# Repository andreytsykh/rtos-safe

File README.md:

# RTOS Safe

> Модель електронного сейфу на ESP32-S3 і FreeRTOS, у якому перезавантаження
> контролера не скидає лічильник невдалих PIN-спроб та активне alarm
> блокування.

## Можливості

- FSM: `LOCKED → ENTERING_CODE → OPEN / ALARM → LOCKED`.
- Введення PIN енкодером із кнопкою та інтерфейс на OLED.
- Три LED, пасивний бузер, реле й SG90 для фізичної індикації та замка.
- Тригодинний `ALARM` після трьох неправильних PIN-кодів.
- Відновлення PIN, лічильника спроб і deadline `ALARM` із FRAM та RTC.
- Миттєве авторизоване скидання `ALARM` NFC-карткою.
- Журнал спроб доступу в окремому розділі flash.
- Структуровані експериментальні Serial-логи з тегом `SAFE_TEST`.

## Апаратна платформа

| Компонент | Призначення |
|---|---|
| ESP32-S3 N16R8, 44 контакти | Контролер і виконання FreeRTOS-задач |
| SSD1306 OLED | Інтерфейс користувача |
| Енкодер із кнопкою | Введення PIN |
| DS1307 | Реальний час і відновлення deadline |
| MB85RC256V FRAM | Енергонезалежний стан і PIN |
| PN532 | NFC-скидання `ALARM` |
| SG90 та реле | Механізм замка й комутація його живлення |
| 2N2222 | Low-level керування входом реле |
| LED та пасивний бузер | Візуальна і звукова індикація |

Логіка живиться від ESP32, а реле й SG90 — від окремого стабілізованого джерела
`+5V_ACT`.

### Програмні компоненти

| Компонент | Версія | Використання | Ліцензія |
|---|---:|---|---|
| [Espressif ESP-IDF](https://github.com/espressif/esp-idf) | 6.0.1 | SDK, FreeRTOS, драйвери й build system | [Apache-2.0](https://github.com/espressif/esp-idf/blob/master/LICENSE) |
| [jef-sure/esp32-component-pn532](https://github.com/jef-sure/esp32-component-pn532) | 0.8.2 | Драйвер PN532 | [MIT](https://github.com/jef-sure/esp32-component-pn532/blob/main/LICENSE) |
| [K0I05 ESP SSD1306](https://github.com/K0I05/ESP32-S3_ESP-IDF_COMPONENTS/tree/main/components/peripherals/i2c/esp_ssd1306) | 1.2.7 | OLED SSD1306 | MIT, згідно з `idf_component.yml` |
| [K0I05 ESP type utils](https://github.com/K0I05/ESP32-S3_ESP-IDF_COMPONENTS/tree/main/components/utilities/esp_type_utils) | 1.2.7 | Допоміжні типи SSD1306-компонента | MIT, згідно з `idf_component.yml` |

Власні компоненти `audio`, `button`, `display` wrapper, `ds1307`, `fram`,
`lock_actuator`, `nfc_reader` wrapper і `rotary_encoder`, а також application
logic розміщені безпосередньо в цьому репозиторії.

## Швидкий старт

### Потрібно

- ESP-IDF `6.0.1`;
- ESP32-S3 toolchain і драйвер USB/UART;
- плата ESP32-S3 з 16 MB flash;
- підключені модулі відповідно до схеми;
- KiCad 10 — лише для перегляду й редагування плати.

### Збірка і прошивання

```bash
git clone https://github.com/andreytsykh/rtos-safe.git
cd rtos-safe
idf.py set-target esp32s3
idf.py build
idf.py -p <COM port num> flash monitor
```

### Основні параметри

Налаштування GPIO, тривалості таймерів, UID адміністративної картки та режиму
персистентності розміщені в [`main/include/config.h`](main/include/config.h).

```c
#define APP_PERSISTENT_STORAGE_ENABLED 1
```

## Архітектура

- **Peripheral layer:** драйвери енкодера, кнопки, OLED, RTC, FRAM, PN532,
  індикації, аудіо та виконавчого механізму.
- **Logic layer:** FSM сейфа і контролер застосунку.
- **Output layer:** OLED, LED, бузер, журнал доступу, реле та SG90.
- **Reliability layer:** черги, таймери, debounce, синхронізація I²C та
  відновлення безпекового стану.

- остання команда виконавчому механізму — 1.

Новий ESP-IDF I²C master driver сам серіалізує транзакції внутрішнім семафором
шини. Додатковий application-level I²C-мьютекс не використовується.

Докладні схеми взаємодії наведені в каталозі
[`documentation/diagrams`](documentation/diagrams).

## Документація

- [Технічний звіт](TECHNICAL_REPORT.md)
- [PCB](/hardware/rtos-safe-controller-v5-3d.png)
- [Карта периферії та GPIO](diagrams/01-peripherals-gpio-map.svg)
- [Шарова архітектура](diagrams/02-layered-architecture.svg)
- [FSM сейфа](diagrams/03-safe-fsm.svg)
- [Топологія FreeRTOS-черг](diagrams/04-queue-topology.svg)
- [Спільні ресурси системи](diagrams/05-shared-resources.svg)
- [MB85RC256V FRAM — datasheet](https://arduino.ua/files/MB85RC256V-20171207.pdf?srsltid=AYCX9vIUnYzoN1OLDvsHvFVYcb9_M5UWzZKLhw7NTm0MXg6MB3GTpYQI)
- [PN532 NFC controller — офіційний datasheet NXP](https://www.nxp.com/docs/en/nxp/data-sheets/PN532_C1.pdf)
- [Історія змін](CHANGELOG.md)

## Технологічний стек

- C23, CMake, ESP-IDF 6.0.1;
- FreeRTOS: задачі, черги, software timers і синхронізація;
- I²C, LEDC PWM, PCNT/GPIO, UART console;
- KiCad 10 і двошарова PCB;
- Graphviz для архітектурних діаграм.

## Автор

**Andrii Tsykhmeistruk** — [@andreytsykh](https://github.com/andreytsykh).

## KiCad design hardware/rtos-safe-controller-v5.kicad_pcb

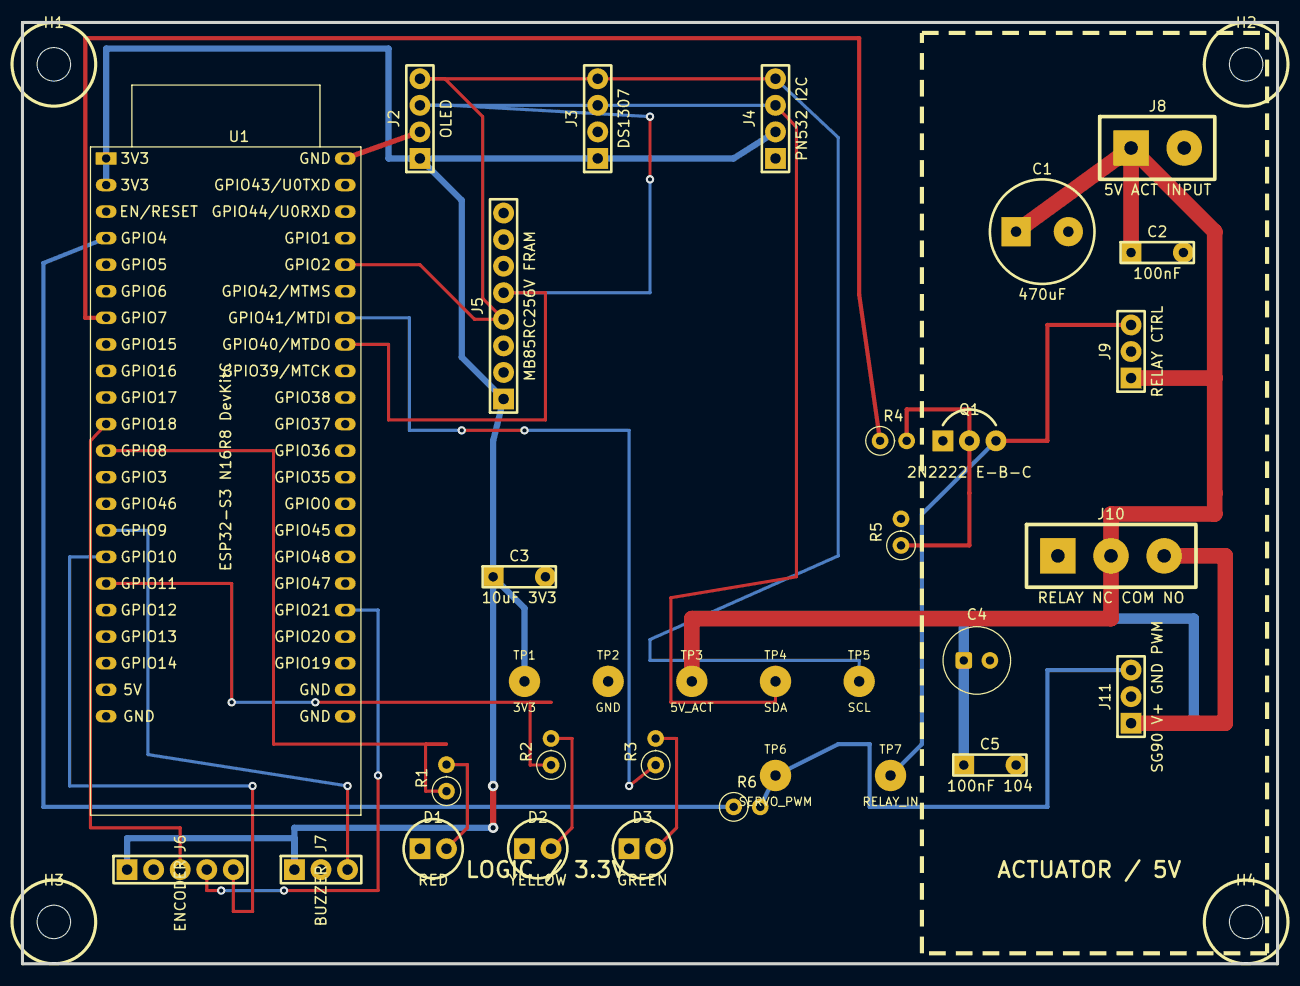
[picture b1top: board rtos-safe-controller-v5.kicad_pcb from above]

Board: 2 copper layers, 120.0 x 90.0 mm, 37 parts (0 on the bottom side), 21 nets.

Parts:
C1: 470uF; CP_Radial_D10.0mm_P5.00mm
C2: 100nF; C_Disc_D5.0mm_W2.5mm_P5.00mm
C3: 10uF 3V3; C_Disc_D5.0mm_W2.5mm_P5.00mm
C4: 100uF_16V; CP_Radial_D6.3mm_P2.50mm
C5: 100nF 104; C_Disc_D5.0mm_W2.5mm_P5.00mm
D1: RED; LED_D5.0mm
D2: YELLOW; LED_D5.0mm
D3: GREEN; LED_D5.0mm
H1, H2, H3, H4: M3; MountingHole_3.2mm_M3
J2: OLED; PinSocket_1x04_P2.54mm_Vertical
J3: DS1307; PinSocket_1x04_P2.54mm_Vertical
J4: PN532 I2C; PinSocket_1x04_P2.54mm_Vertical
J5: MB85RC256V FRAM; PinSocket_1x08_P2.54mm_Vertical
J6: ENCODER; PinSocket_1x05_P2.54mm_Vertical
J7: BUZZER; PinSocket_1x03_P2.54mm_Vertical
J8: 5V ACT INPUT; TerminalBlock_bornier-2_P5.08mm
J9: RELAY CTRL; PinSocket_1x03_P2.54mm_Vertical
J10: RELAY NC COM NO; TerminalBlock_bornier-3_P5.08mm
J11: SG90 V+ GND PWM; PinHeader_1x03_P2.54mm_Vertical
Q1: 2N2222 E-B-C; TO-92_Inline
R1, R2, R3: 330R; R_Axial_DIN0207_L6.3mm_D2.5mm_P2.54mm_Vertical
R4, R6: 1k; R_Axial_DIN0207_L6.3mm_D2.5mm_P2.54mm_Vertical
R5: 10k; R_Axial_DIN0207_L6.3mm_D2.5mm_P2.54mm_Vertical
TP1: 3V3; TestPoint_THTPad_D2.0mm_Drill1.0mm
TP2: GND; TestPoint_THTPad_D2.0mm_Drill1.0mm
TP3: 5V_ACT; TestPoint_THTPad_D2.0mm_Drill1.0mm
TP4: SDA; TestPoint_THTPad_D2.0mm_Drill1.0mm
TP5: SCL; TestPoint_THTPad_D2.0mm_Drill1.0mm
TP6: SERVO_PWM; TestPoint_THTPad_D2.0mm_Drill1.0mm
TP7: RELAY_IN; TestPoint_THTPad_D2.0mm_Drill1.0mm
U1: ESP32-S3 N16R8 DevKitC; ESP32-S3-DevKitC

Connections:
+3V3: C3.1, J2.1, J3.1, J4.2, J5.1, J6.1, J7.1, TP1.1, U1.1, U1.2
+5V_ACT: C1.1, C2.1, J8.1, J9.1, J10.2, TP3.1
BUZZER_PWM: J7.3, U1.15
ENC_A: J6.3, U1.11
ENC_B: J6.4, U1.27
ENC_SW: J6.5, U1.16
GND: C1.2, C2.2, C3.2, C4.2, C5.2, D1.1, D2.1, D3.1, J2.2, J3.2, J4.1, J5.2, J5.3, J5.6, J5.7, J5.8, J6.2, J7.2, J8.2, J9.2, J11.2, Q1.1, R5.2, TP2.1, U1.22, U1.23, U1.24, U1.44
I2C_SCL: J2.4, J3.4, J4.4, J5.4, TP5.1, U1.40
I2C_SDA: J2.3, J3.3, J4.3, J5.5, TP4.1, U1.37
LED_GREEN: R3.1, U1.38
LED_GREEN_A: D3.2, R3.2
LED_RED: R1.1, U1.12
LED_RED_A: D1.2, R1.2
LED_YELLOW: R2.1, U1.17
LED_YELLOW_A: D2.2, R2.2
RELAY_BASE: Q1.2, R4.2, R5.1
RELAY_CTRL: R4.1, U1.7
RELAY_IN_LOW: J9.3, Q1.3, TP7.1
SERVO_5V_SWITCHED: C4.1, C5.1, J10.3, J11.1
SERVO_PWM: J11.3, R6.2, TP6.1
SERVO_PWM_GPIO: R6.1, U1.4
